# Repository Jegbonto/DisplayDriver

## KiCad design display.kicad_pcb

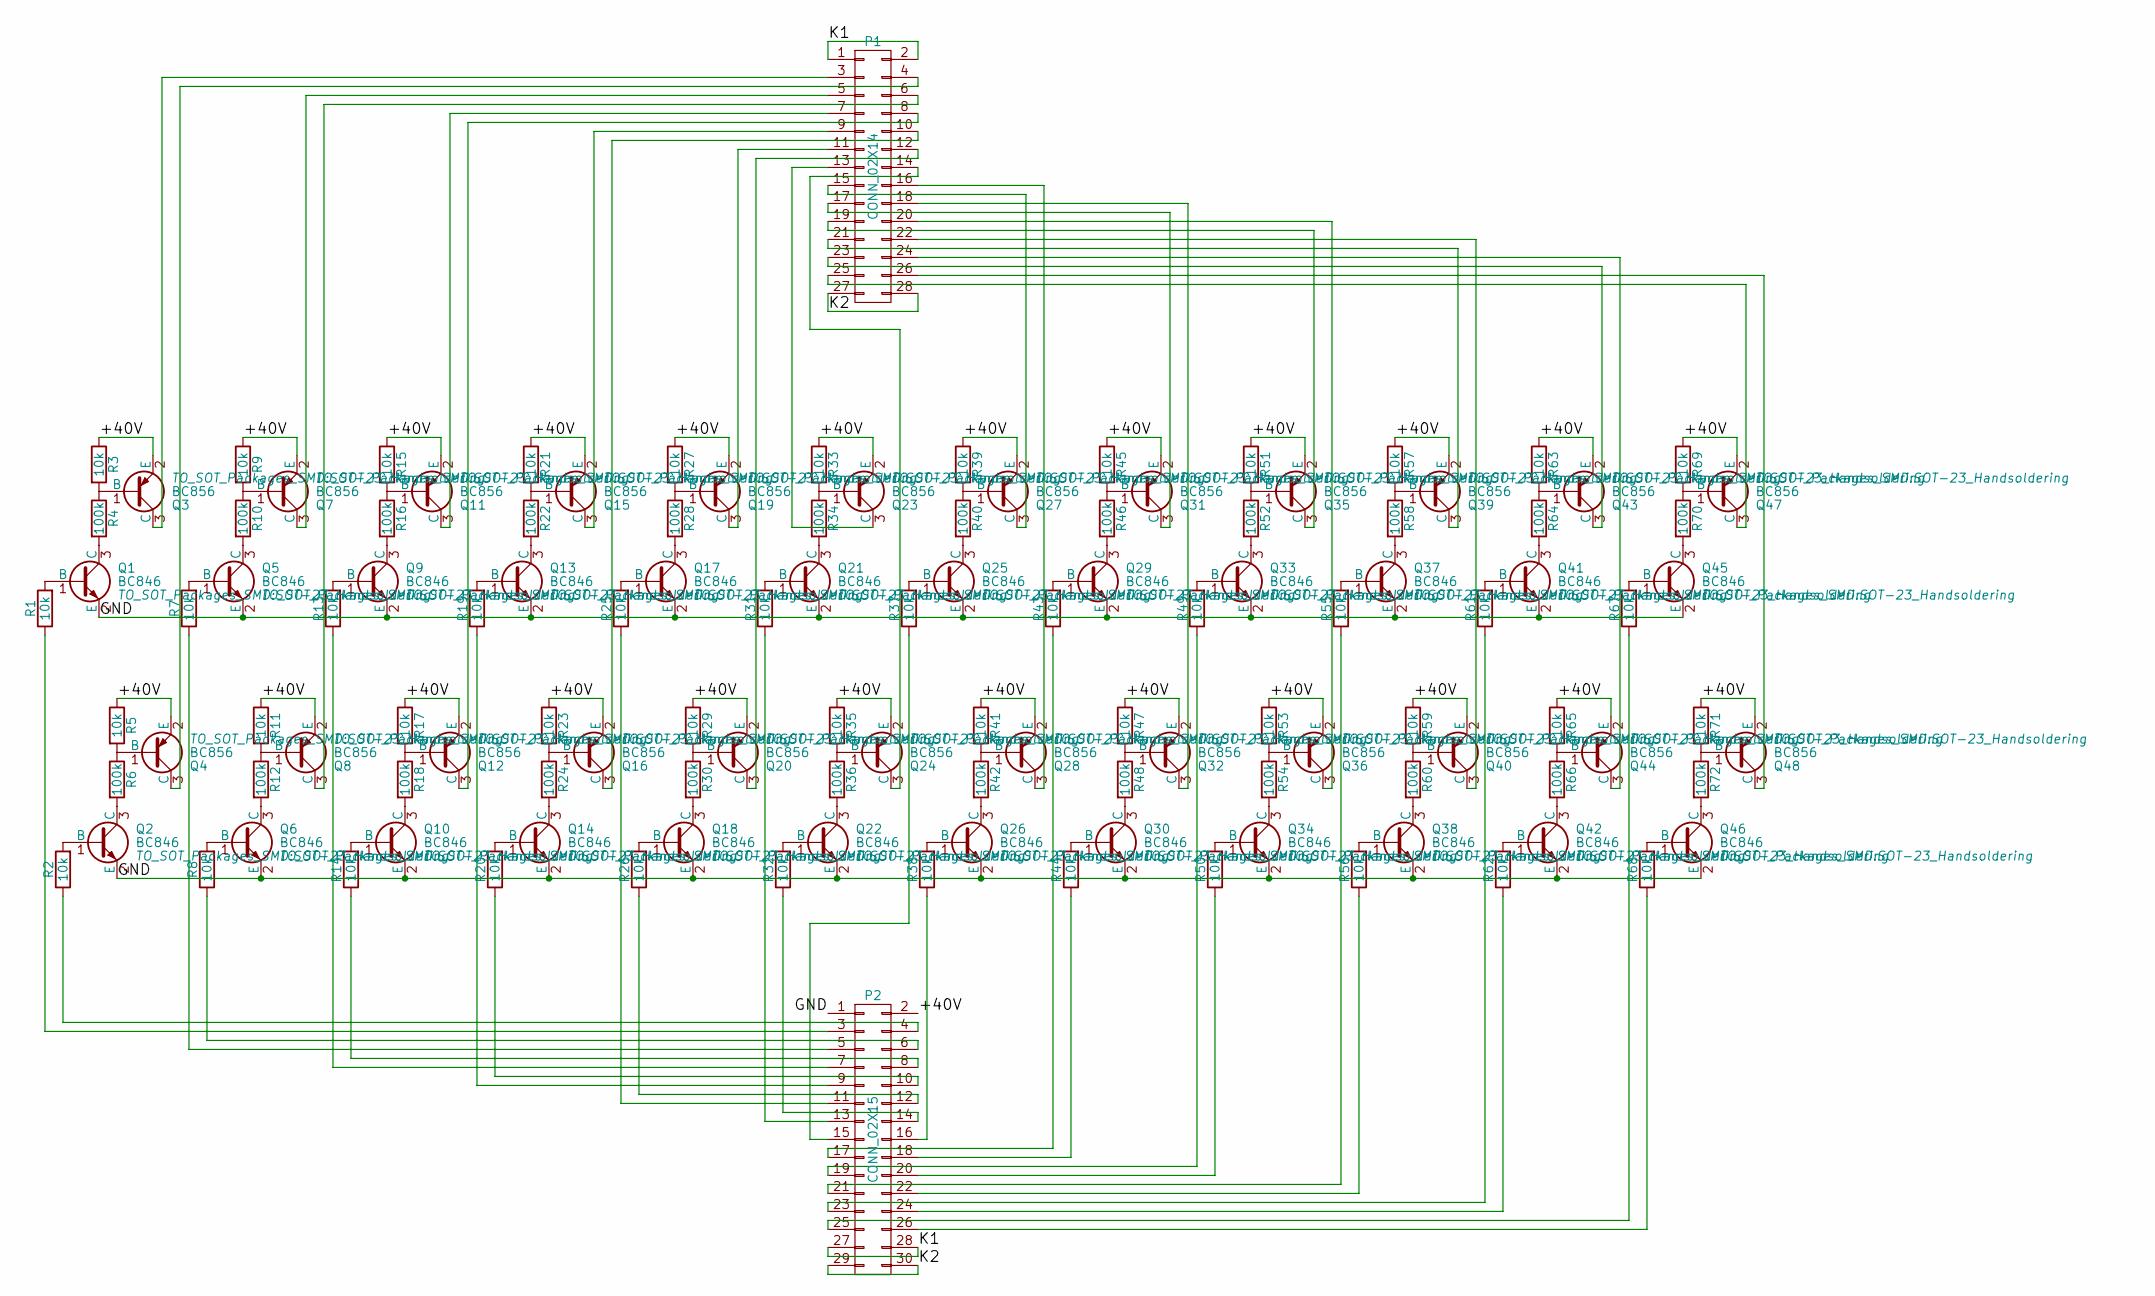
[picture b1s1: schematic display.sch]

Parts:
P1: CONN_02X14; Pin_Header_Straight_2x14
P2: CONN_02X15; Pin_Header_Straight_2x15
Q1, Q2, Q5, Q6, Q9, Q10, Q13, Q14, Q17, Q18, Q21, Q22, Q25, Q26, Q29, Q30, Q33, Q34, Q37, Q38, Q41, Q42, Q45, Q46: BC846; SOT-23_Handsoldering
Q3, Q4, Q7, Q8, Q11, Q12, Q15, Q16, Q19, Q20, Q23, Q24, Q27, Q28, Q31, Q32, Q35, Q36, Q39, Q40, Q43, Q44, Q47, Q48: BC856; SOT-23_Handsoldering
R1, R2, R3, R5, R7, R8, R9, R11, R13, R14, R15, R17, R19, R20, R21, R23, R25, R26, R27, R29, R31, R32, R33, R35, R37, R38, R39, R41, R43, R44, R45, R47, R49, R50, R51, R53, R55, R56, R57, R59, R61, R62, R63, R65, R67, R68, R69, R71: 10k; R_0805_HandSoldering
R4, R6, R10, R12, R16, R18, R22, R24, R28, R30, R34, R36, R40, R42, R46, R48, R52, R54, R58, R60, R64, R66, R70, R72: 100k; R_0805_HandSoldering

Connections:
/+40V: P2.2, Q3.2 (E), Q4.2 (E), Q7.2 (E), Q8.2 (E), Q11.2 (E), Q12.2 (E), Q15.2 (E), Q16.2 (E), Q19.2 (E), Q20.2 (E), Q23.2 (E), Q24.2 (E), Q27.2 (E), Q28.2 (E), Q31.2 (E), Q32.2 (E), Q35.2 (E), Q36.2 (E), Q39.2 (E), Q40.2 (E), Q43.2 (E), Q44.2 (E), Q47.2 (E), Q48.2 (E), R3.1, R5.1, R9.1, R11.1, R15.1, R17.1, R21.1, R23.1, R27.1, R29.1, R33.1, R35.1, R39.1, R41.1, R45.1, R47.1, R51.1, R53.1, R57.1, R59.1, R63.1, R65.1, R69.1, R71.1
/GND: P2.1, Q1.2 (E), Q2.2 (E), Q5.2 (E), Q6.2 (E), Q9.2 (E), Q10.2 (E), Q13.2 (E), Q14.2 (E), Q17.2 (E), Q18.2 (E), Q21.2 (E), Q22.2 (E), Q25.2 (E), Q26.2 (E), Q29.2 (E), Q30.2 (E), Q33.2 (E), Q34.2 (E), Q37.2 (E), Q38.2 (E), Q41.2 (E), Q42.2 (E), Q45.2 (E), Q46.2 (E)
/K1: P1.1, P1.2, P2.27, P2.28
/K2: P1.27, P1.28, P2.29, P2.30
unnamed: P1.3, Q3.3 (C)
unnamed: P1.4, Q4.3 (C)
unnamed: P1.5, Q7.3 (C)
unnamed: P1.6, Q8.3 (C)
unnamed: P1.7, Q11.3 (C)
unnamed: P1.8, Q12.3 (C)
unnamed: P1.9, Q15.3 (C)
unnamed: P1.10, Q16.3 (C)
unnamed: P1.11, Q19.3 (C)
unnamed: P1.12, Q20.3 (C)
unnamed: P1.13, Q23.3 (C)
unnamed: P1.14, Q24.3 (C)
unnamed: P1.15, Q27.3 (C)
unnamed: P1.16, Q28.3 (C)
unnamed: P1.17, Q31.3 (C)
unnamed: P1.18, Q32.3 (C)
unnamed: P1.19, Q35.3 (C)
unnamed: P1.20, Q36.3 (C)
unnamed: P1.21, Q39.3 (C)
unnamed: P1.22, Q40.3 (C)
unnamed: P1.23, Q43.3 (C)
unnamed: P1.24, Q44.3 (C)
unnamed: P1.25, Q47.3 (C)
unnamed: P1.26, Q48.3 (C)
unnamed: P2.3, R1.1
unnamed: P2.4, R2.1
unnamed: P2.5, R7.1
unnamed: P2.6, R8.1
unnamed: P2.7, R13.1
unnamed: P2.8, R14.1
unnamed: P2.9, R19.1
unnamed: P2.10, R20.1
unnamed: P2.11, R25.1
unnamed: P2.12, R26.1
unnamed: P2.13, R31.1
unnamed: P2.14, R32.1
unnamed: P2.15, R37.1
unnamed: P2.16, R38.1
unnamed: P2.17, R43.1
unnamed: P2.18, R44.1
unnamed: P2.19, R49.1
unnamed: P2.20, R50.1
unnamed: P2.21, R55.1
unnamed: P2.22, R56.1
unnamed: P2.23, R61.1
unnamed: P2.24, R62.1
unnamed: P2.25, R67.1
unnamed: P2.26, R68.1
unnamed: Q1.1 (B), R1.2
unnamed: Q1.3 (C), R4.2
unnamed: Q2.1 (B), R2.2
unnamed: Q2.3 (C), R6.2
unnamed: Q3.1 (B), R3.2, R4.1
unnamed: Q4.1 (B), R5.2, R6.1
unnamed: Q5.1 (B), R7.2
unnamed: Q5.3 (C), R10.2
unnamed: Q6.1 (B), R8.2
unnamed: Q6.3 (C), R12.2
unnamed: Q7.1 (B), R9.2, R10.1
unnamed: Q8.1 (B), R11.2, R12.1
unnamed: Q9.1 (B), R13.2
unnamed: Q9.3 (C), R16.2
unnamed: Q10.1 (B), R14.2
unnamed: Q10.3 (C), R18.2
unnamed: Q11.1 (B), R15.2, R16.1
unnamed: Q12.1 (B), R17.2, R18.1
unnamed: Q13.1 (B), R19.2
unnamed: Q13.3 (C), R22.2
unnamed: Q14.1 (B), R20.2
unnamed: Q14.3 (C), R24.2
unnamed: Q15.1 (B), R21.2, R22.1
unnamed: Q16.1 (B), R23.2, R24.1
unnamed: Q17.1 (B), R25.2
unnamed: Q17.3 (C), R28.2
unnamed: Q18.1 (B), R26.2
unnamed: Q18.3 (C), R30.2
unnamed: Q19.1 (B), R27.2, R28.1
unnamed: Q20.1 (B), R29.2, R30.1
unnamed: Q21.1 (B), R31.2
unnamed: Q21.3 (C), R34.2
unnamed: Q22.1 (B), R32.2
unnamed: Q22.3 (C), R36.2
unnamed: Q23.1 (B), R33.2, R34.1
unnamed: Q24.1 (B), R35.2, R36.1
unnamed: Q25.1 (B), R37.2
unnamed: Q25.3 (C), R40.2
unnamed: Q26.1 (B), R38.2
unnamed: Q26.3 (C), R42.2
unnamed: Q27.1 (B), R39.2, R40.1
unnamed: Q28.1 (B), R41.2, R42.1
unnamed: Q29.1 (B), R43.2
unnamed: Q29.3 (C), R46.2
unnamed: Q30.1 (B), R44.2
unnamed: Q30.3 (C), R48.2
unnamed: Q31.1 (B), R45.2, R46.1
unnamed: Q32.1 (B), R47.2, R48.1
unnamed: Q33.1 (B), R49.2
unnamed: Q33.3 (C), R52.2
unnamed: Q34.1 (B), R50.2
unnamed: Q34.3 (C), R54.2
unnamed: Q35.1 (B), R51.2, R52.1
unnamed: Q36.1 (B), R53.2, R54.1
unnamed: Q37.1 (B), R55.2
unnamed: Q37.3 (C), R58.2
unnamed: Q38.1 (B), R56.2
unnamed: Q38.3 (C), R60.2
unnamed: Q39.1 (B), R57.2, R58.1
unnamed: Q40.1 (B), R59.2, R60.1
unnamed: Q41.1 (B), R61.2
unnamed: Q41.3 (C), R64.2
unnamed: Q42.1 (B), R62.2
unnamed: Q42.3 (C), R66.2
unnamed: Q43.1 (B), R63.2, R64.1
unnamed: Q44.1 (B), R65.2, R66.1
unnamed: Q45.1 (B), R67.2
unnamed: Q45.3 (C), R70.2
unnamed: Q46.1 (B), R68.2
unnamed: Q46.3 (C), R72.2
unnamed: Q47.1 (B), R69.2, R70.1
unnamed: Q48.1 (B), R71.2, R72.1

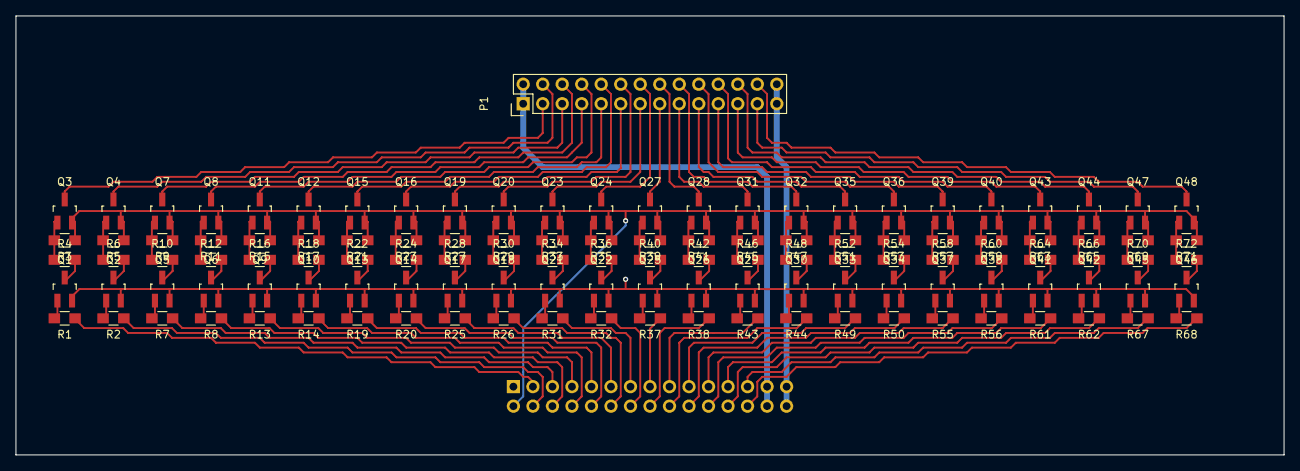
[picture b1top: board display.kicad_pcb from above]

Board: 2 copper layers, 165.1 x 57.1 mm, 122 parts (1 on the bottom side), 124 nets.

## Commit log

2016-11-08 :neckbeard: Added .gitattributes & .gitignore files
2016-11-08 Initial State
2016-11-08 Placement finalizing and some small routing.
2016-11-08 Finishing layout, generating gerbers.
